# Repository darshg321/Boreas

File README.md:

# Boreas

a flight controller for a rocket.

made this project to both learn how to make flight controllers in general for my drone. making it i got some more practice in routing pcbs and how to read datasheets!
the plan for this board is to be used in a rocket im going to make, where hopefully with the gyro and motor pins i can get it to 1km altitude or higher. little ambitious for my first rocket project but i tihnk it should be fine! for its kind of a big pcb so it'll be hard to fit on the rocket but itll work fine i think. also the sd card will be useful to gain cool telemetry, and i plan to use it to generate interesting graphs that can tell me how to improve the rocket further.

it uses an STM32F7 as an mcu, connected to an imu, barometer, and magnometer. it also has 3 leds, two buttons, a buzzer, and 3 servo motor pins. it can also charge lipo batteries through usb-c! lastly it has an sd card reader for data display!

## Poster (Zine)

## Render

## Schematic

## PCB

## To use

1. plug assembled PCB into computer
2. run ```make flash``` in firmware path after pressing boot and reset buttons to enter flashing mode on the STM32

## BOM

|Item    |Price (USD)|
|--------|-----------|
|PCB     |2          |
|PCBA    |198.65     |
|Shipping|26.51      |
|        |           |
|Total   |227.16     |

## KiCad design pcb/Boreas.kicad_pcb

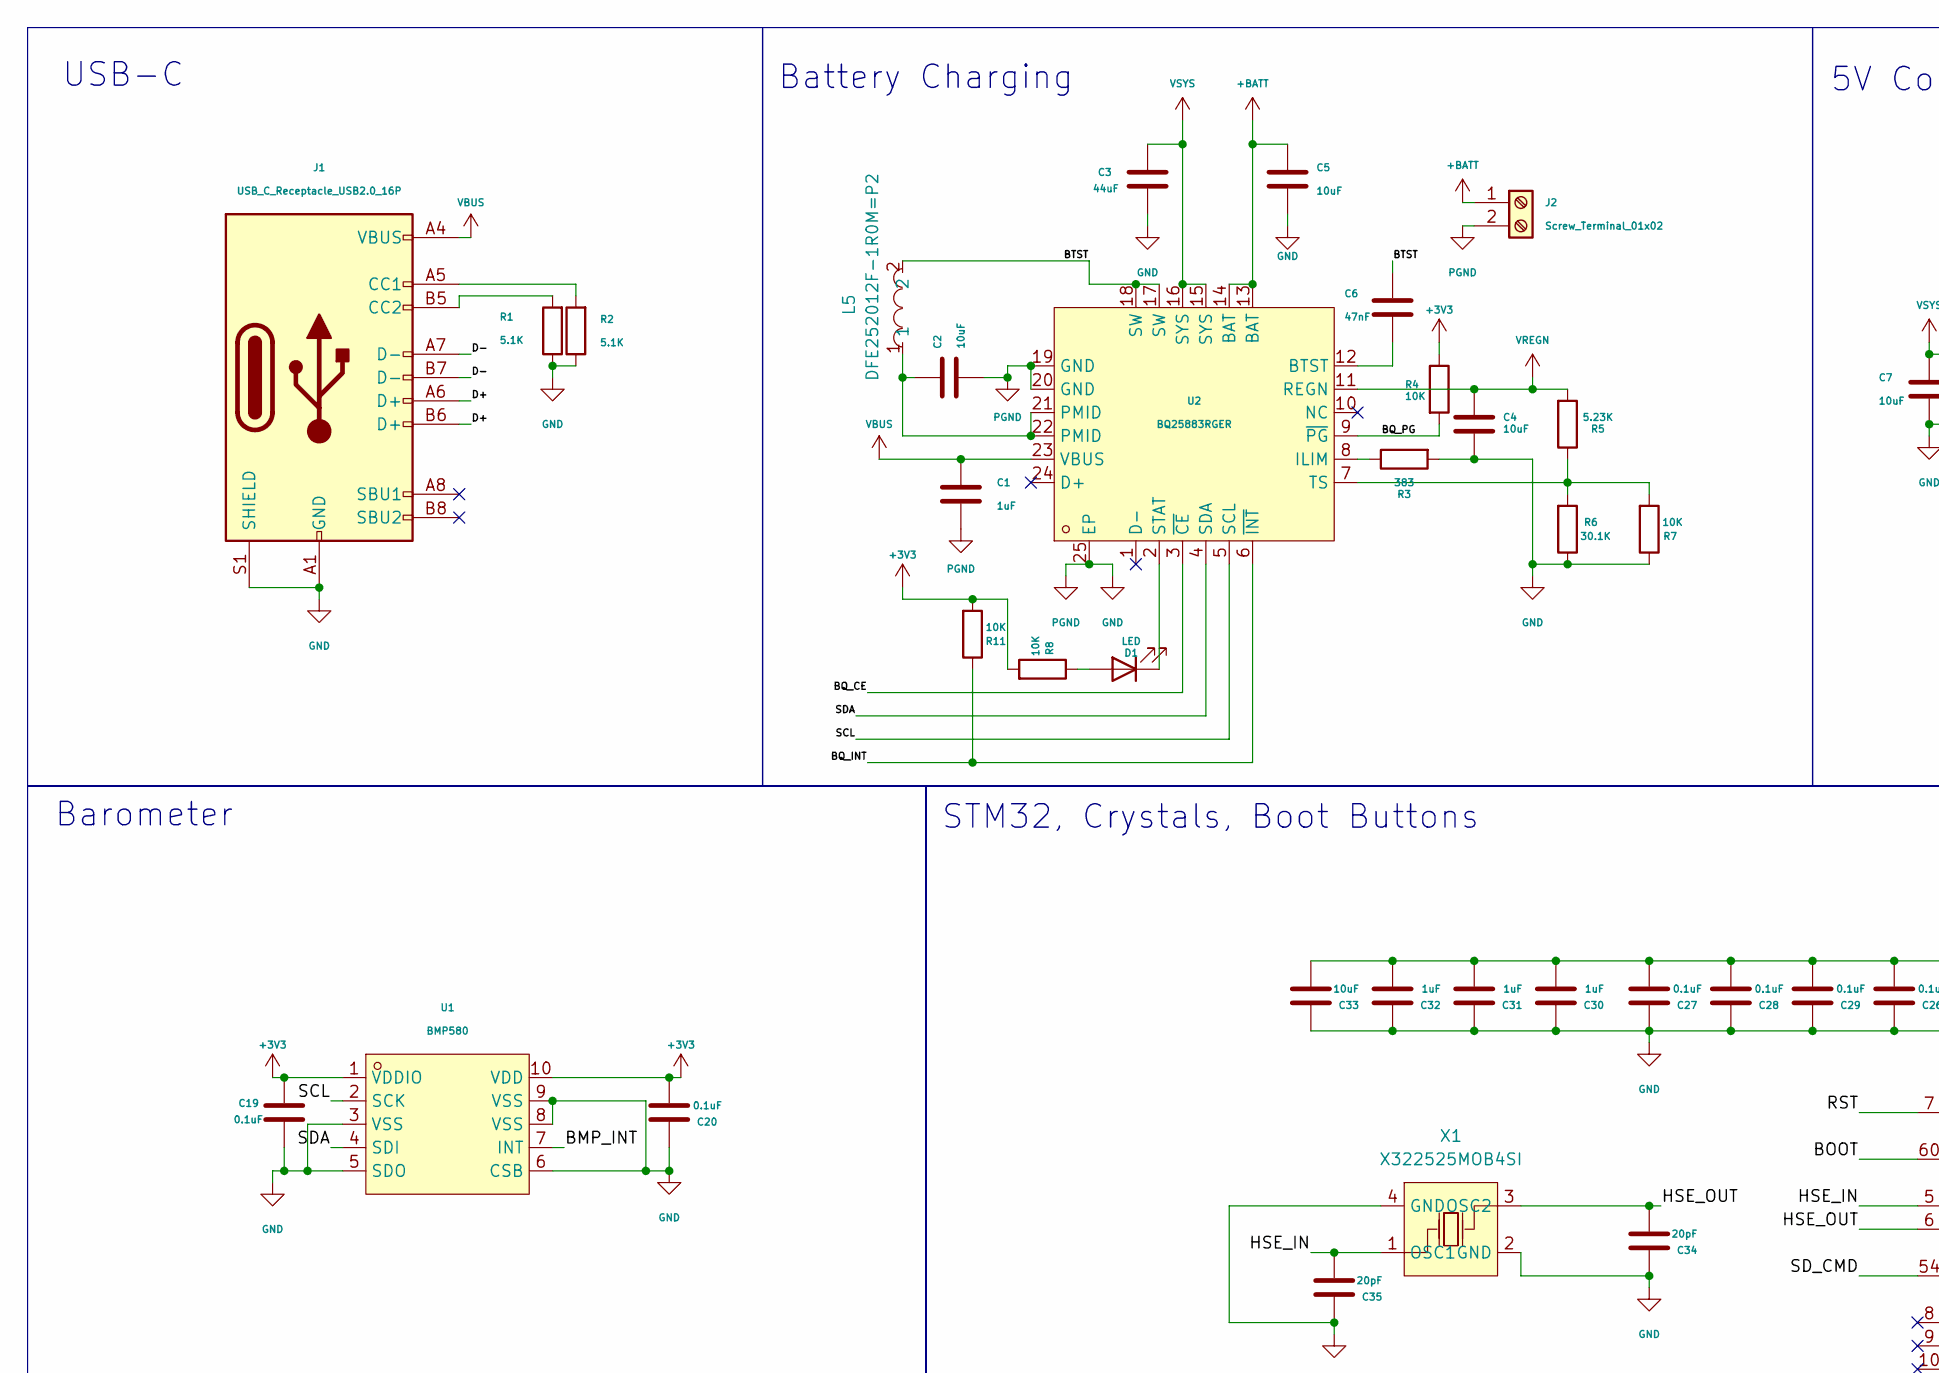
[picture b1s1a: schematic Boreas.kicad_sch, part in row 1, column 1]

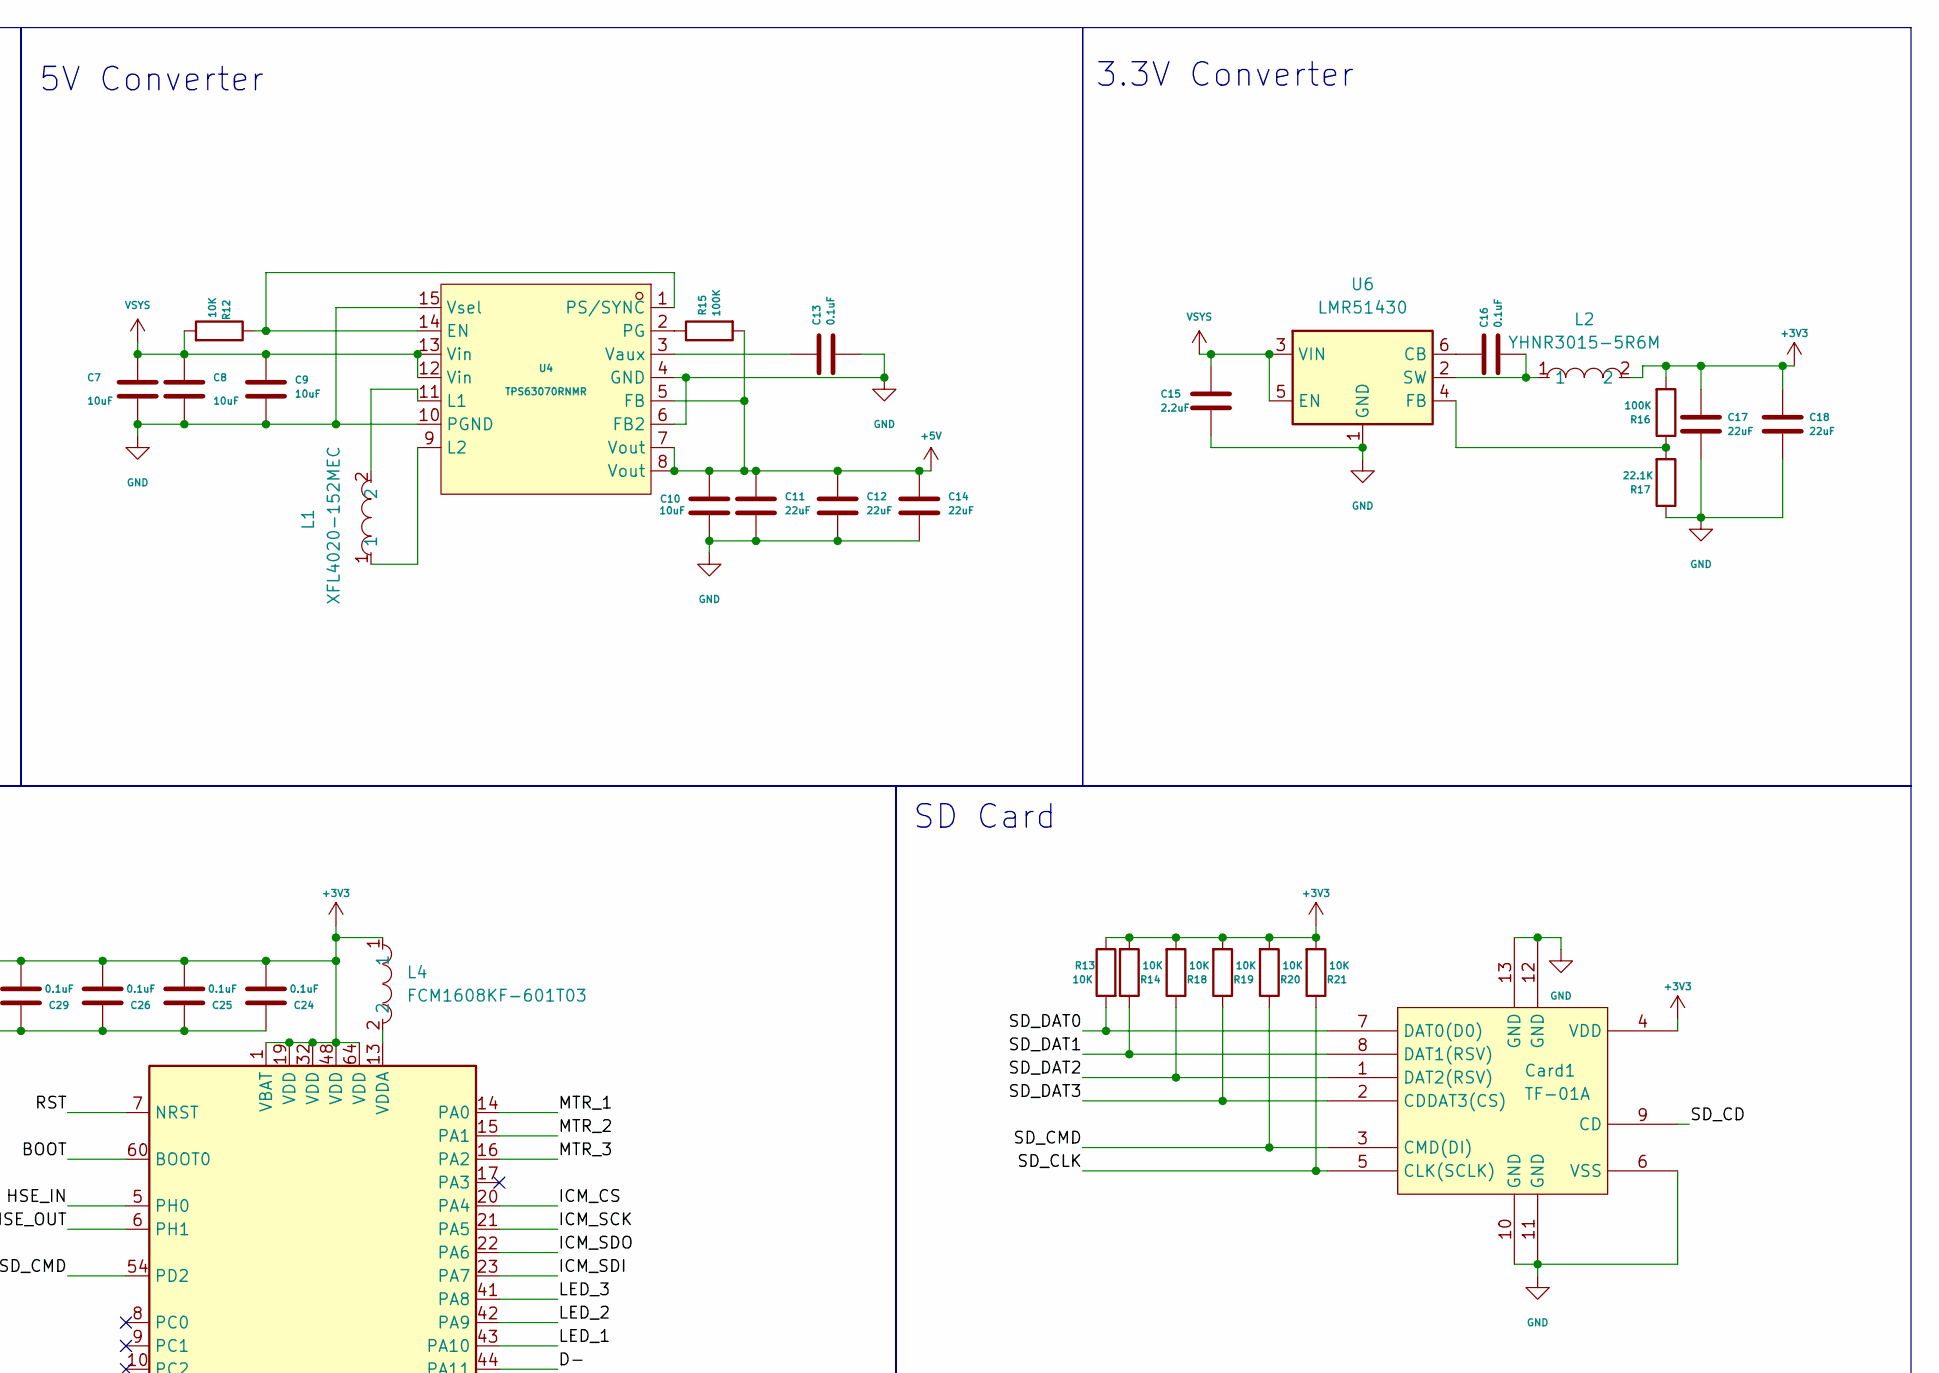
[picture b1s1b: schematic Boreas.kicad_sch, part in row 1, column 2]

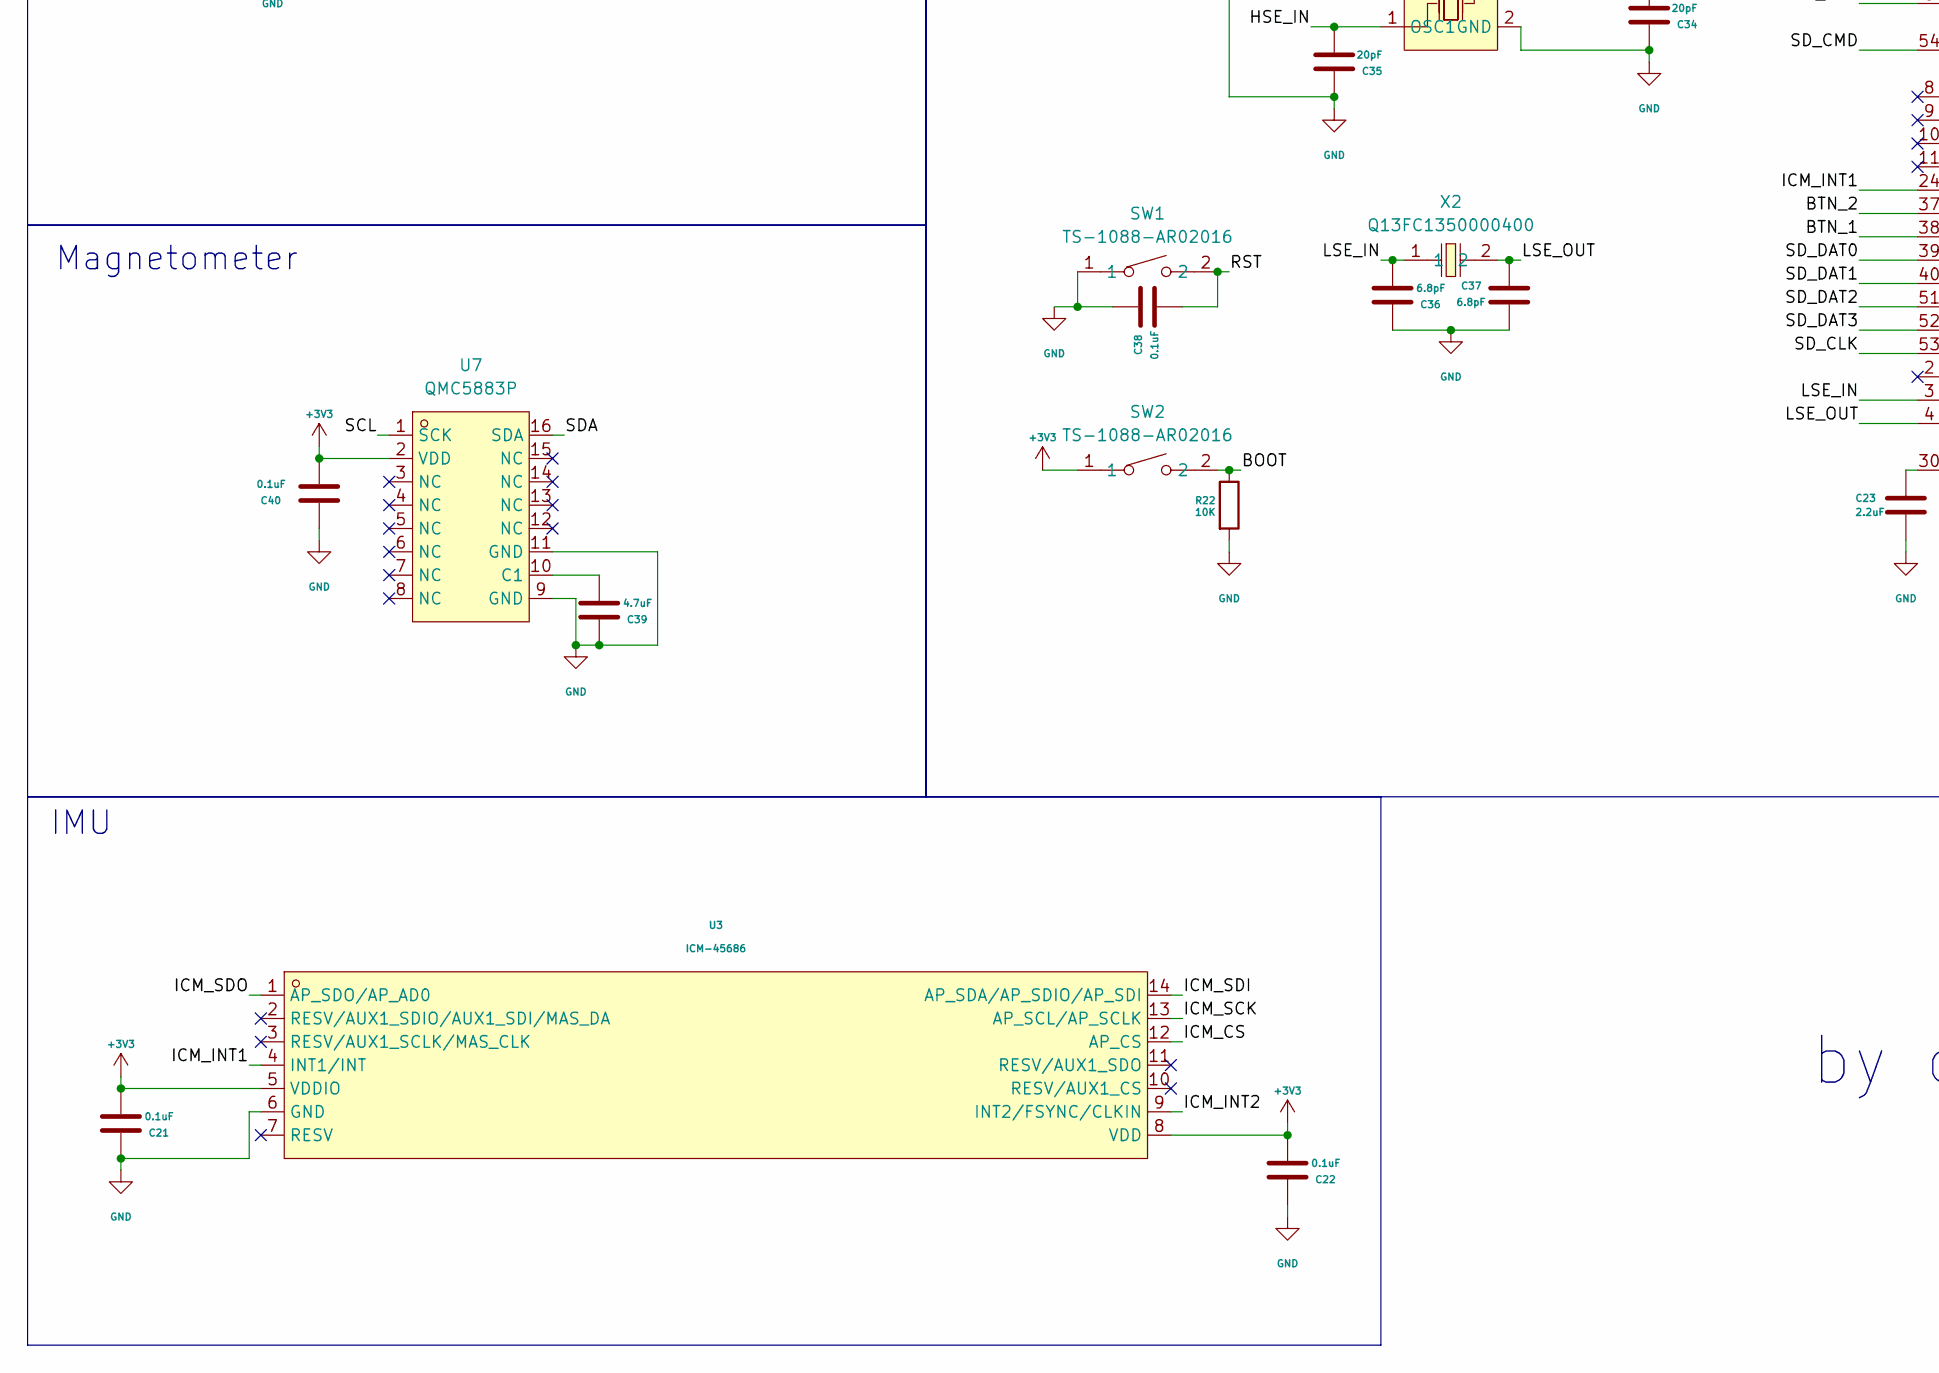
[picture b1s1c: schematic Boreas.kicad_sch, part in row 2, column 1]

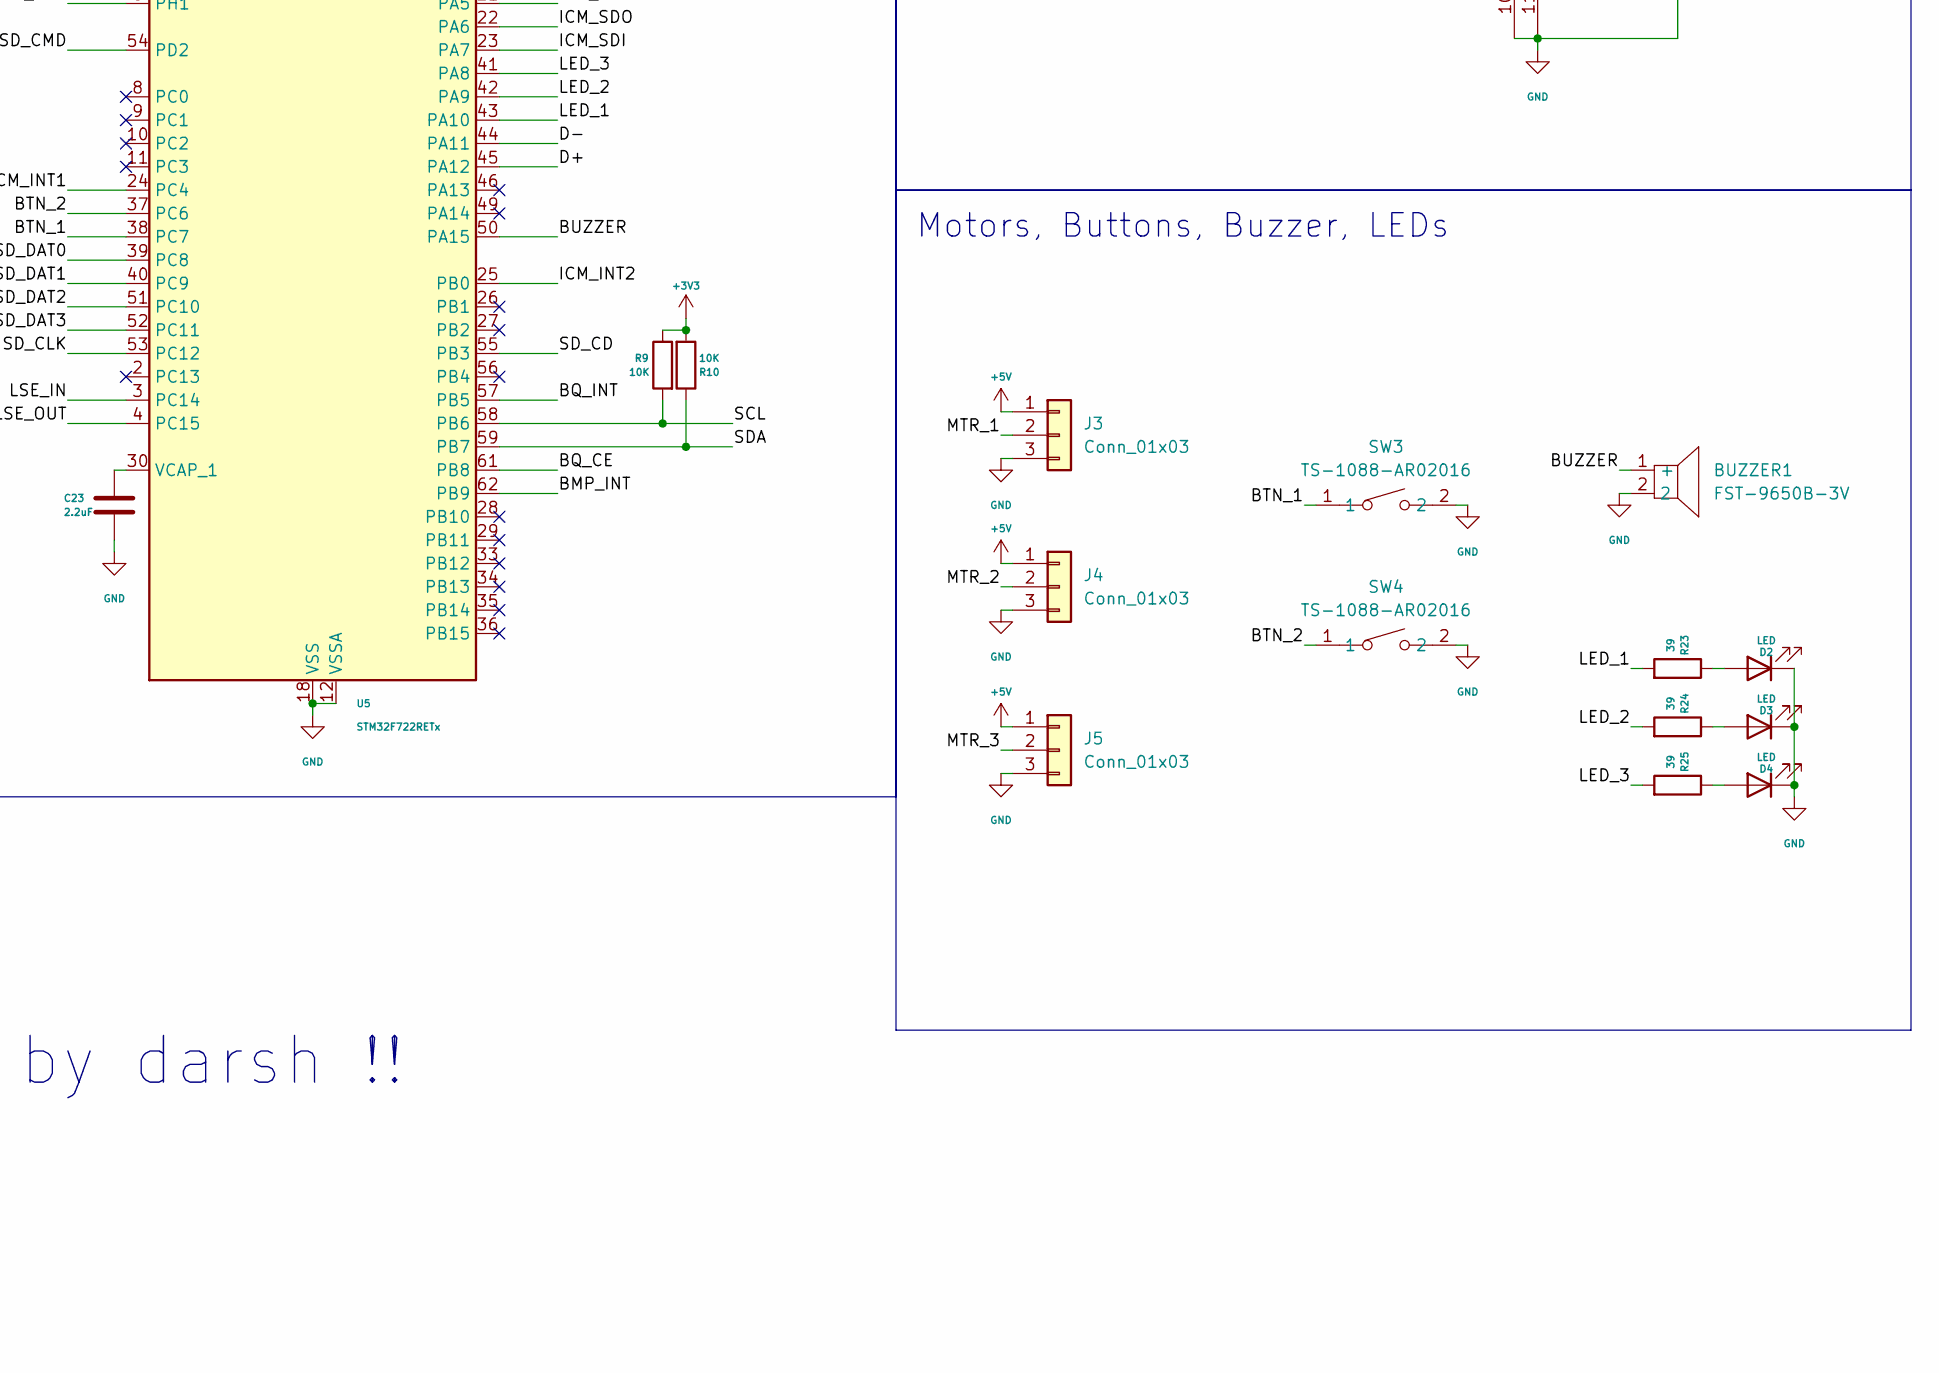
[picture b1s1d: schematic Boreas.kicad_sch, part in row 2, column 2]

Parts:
BUZZER1: FST-9650B-3V; BUZ-SMD_L9.6-W9.6-LS10.0-R; MPN FUET-9650B-3V; LCSC Part C391032
C1, C30, C31, C32: 1uF; C_0402_1005Metric
C2, C4, C5, C7, C8, C9, C10, C33: 10uF; C_0603_1608Metric
C3: 44uF; C_0805_2012Metric
C6: 47nF; C_0402_1005Metric
C11, C12, C14, C17, C18: 22uF; C_0805_2012Metric
C13, C16, C19, C20, C21, C22, C24, C25, C26, C27, C28, C29, C38, C40: 0.1uF; C_0402_1005Metric
C15, C23: 2.2uF; C_0402_1005Metric
C34, C35: 20pF; C_0402_1005Metric
C36, C37: 6.8pF; C_0402_1005Metric
C39: 4.7uF; C_0603_1608Metric
Card1: TF-01A; TF-SMD_TF-01A; MPN TF-01A; LCSC Part C91145
D1, D2, D3, D4: LED; LED_0603_1608Metric
J1: USB_C_Receptacle_USB2.0_16P; USB_C_Receptacle_HRO_TYPE-C-31-M-12
J2: Screw_Terminal_01x02; TerminalBlock_Xinya_XY308-2.54-2P_1x02_P2.54mm_Horizontal
J3, J4, J5: Conn_01x03; PinHeader_1x03_P2.54mm_Vertical
L1: XFL4020-152MEC; IND-SMD_L4.0-W4.0-A; MPN XFL4020-152MEC; LCSC Part C3033018
L2: YHNR3015-5R6M; IND-SMD_L3.0-W3.0; MPN YHNR3015-5R6M; LCSC Part C18236327
L4: FCM1608KF-601T03; L0603; MPN FCM1608KF-601T03; LCSC Part C141723
L5: DFE252012F-1R0M=P2; L2520; MPN DFE252012F-1R0M=P2; LCSC Part C435392
R1, R2: 5.1K; R_0402_1005Metric
R3: 383; R_0402_1005Metric
R4, R7, R8, R9, R10, R11, R12, R13, R14, R18, R19, R20, R21, R22: 10K; R_0402_1005Metric
R5: 5.23K; R_0402_1005Metric
R6: 30.1K; R_0402_1005Metric
R15, R16: 100K; R_0402_1005Metric
R17: 22.1K; R_0402_1005Metric
R23, R24, R25: 39; R_0402_1005Metric
SW1, SW2, SW3, SW4: TS-1088-AR02016; SW-SMD_L3.9-W3.0-P4.45; MPN TS-1088-AR02016; LCSC Part C720477
U1: BMP580; LGA-10_L2.0-W2.0-P0.50-TL_BMP580; MPN BMP580; LCSC Part C22391138
U2: BQ25883RGER; VFQFPN-24_L4.0-W4.0-P0.50-BL-EP2.8; MPN BQ25883RGER; LCSC Part C544362
U3: ICM-45686; LGA-14_L3.0-W2.5-P0.50-TL; MPN ICM-45686; LCSC Part C22459454
U4: TPS63070RNMR; VQFN-15_L3.0-W2.5-P0.50-BL; MPN TPS63070RNMR; LCSC Part C109322
U5: STM32F722RETx; LQFP-64_10x10mm_P0.5mm
U6: LMR51430; SOT-23-6
U7: QMC5883P; LGA-16_L3.0-W3.0-P0.50-BL_SQ; MPN QMC5883P; LCSC Part C2847467
X1: X322525MOB4SI; CRYSTAL-SMD_4P-L3.2-W2.5-BL; MPN X322525MOB4SI; LCSC Part C9006
X2: Q13FC1350000400; FC-135R_L3.2-W1.5; MPN Q13FC13500004; LCSC Part C32346

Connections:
+3V3: C17.1, C18.1, C19.1, C20.2, C21.2, C22.2, C24.2, C25.2, C26.2, C27.2, C28.2, C29.2, C30.2, C31.2, C32.2, C33.2, C40.2, Card1.4 (VDD), L2.2, L4.1, R4.1, R8.2, R9.1, R10.2, R11.2, R13.1, R14.2, R16.2, R18.2, R19.2, R20.2, R21.2, SW2.1, U1.1 (VDDIO), U1.10 (VDD), U3.5 (VDDIO), U3.8 (VDD), U5.1 (VBAT), U5.19 (VDD), U5.32 (VDD), U5.48 (VDD), U5.64 (VDD), U7.2 (VDD)
+5V: C10.2, C11.1, C12.1, C14.1, J3.1, J4.1, J5.1, R15.2, U4.5 (FB), U4.7 (Vout), U4.8 (Vout)
+BATT: C5.1, J2.1, U2.13 (BAT), U2.14 (BAT)
/BMP_INT: U1.7 (INT), U5.62 (PB9)
/BOOT: R22.1, SW2.2, U5.60 (BOOT0)
/BQ_CE: U2.3 (~CE), U5.61 (PB8)
/BQ_INT: R11.1, U2.6 (~INT), U5.57 (PB5)
/BQ_PG: R4.2, U2.9 (~PG)
/BTN_1: SW3.1, U5.38 (PC7)
/BTN_2: SW4.1, U5.37 (PC6)
/BTST: C6.1, L5.2, U2.17 (SW), U2.18 (SW)
/BUZZER: BUZZER1.1 (+), U5.50 (PA15)
/D+: J1.A6 (D+), J1.B6 (D+), U5.45 (PA12)
/D-: J1.A7 (D-), J1.B7 (D-), U5.44 (PA11)
/HSE_IN: C35.2, U5.5 (PH0), X1.1 (OSC1)
/HSE_OUT: C34.2, U5.6 (PH1), X1.3 (OSC2)
/ICM_CS: U3.12 (AP_CS), U5.20 (PA4)
/ICM_INT1: U3.4 (INT1/INT), U5.24 (PC4)
/ICM_INT2: U3.9 (INT2/FSYNC/CLKIN), U5.25 (PB0)
/ICM_SCK: U3.13 (AP_SCL/AP_SCLK), U5.21 (PA5)
/ICM_SDI: U3.14 (AP_SDA/AP_SDIO/AP_SDI), U5.23 (PA7)
/ICM_SDO: U3.1 (AP_SDO/AP_AD0), U5.22 (PA6)
/LED_1: R23.2, U5.43 (PA10)
/LED_2: R24.2, U5.42 (PA9)
/LED_3: R25.2, U5.41 (PA8)
/LSE_IN: C36.2, U5.3 (PC14), X2.1
/LSE_OUT: C37.1, U5.4 (PC15), X2.2
/MTR_1: J3.2, U5.14 (PA0)
/MTR_2: J4.2, U5.15 (PA1)
/MTR_3: J5.2, U5.16 (PA2)
/RST: C38.2, SW1.2, U5.7 (NRST)
/SCL: R9.2, U1.2 (SCK), U2.5 (SCL), U5.58 (PB6), U7.1 (SCK)
/SDA: R10.1, U1.4 (SDI), U2.4 (SDA), U5.59 (PB7), U7.16 (SDA)
/SD_CD: Card1.9 (CD), U5.55 (PB3)
/SD_CLK: Card1.5 (CLK(SCLK)), R21.1, U5.53 (PC12)
/SD_CMD: Card1.3 (CMD(DI)), R20.1, U5.54 (PD2)
/SD_DAT0: Card1.7 (DAT0(D0)), R13.2, U5.39 (PC8)
/SD_DAT1: Card1.8 (DAT1(RSV)), R14.1, U5.40 (PC9)
/SD_DAT2: Card1.1 (DAT2(RSV)), R18.1, U5.51 (PC10)
/SD_DAT3: Card1.2 (CDDAT3(CS)), R19.1, U5.52 (PC11)
GND: BUZZER1.2, C1.2, C2.2, C3.1, C4.2, C5.2, C7.2, C8.2, C9.2, C10.1, C11.2, C12.2, C13.2, C14.2, C15.2, C17.2, C18.2, C19.2, C20.1, C21.1, C22.1, C23.2, C24.1, C25.1, C26.1, C27.1, C28.1, C29.1, C30.1, C31.1, C32.1, C33.1, C34.1, C35.1, C36.1, C37.2, C38.1, C39.1, C40.1, Card1.6 (VSS), Card1.10 (GND), Card1.11 (GND), Card1.12 (GND), Card1.13 (GND), D2.1 (K), D3.1 (K), D4.1 (K), J1.A1 (GND), J1.A12 (GND), J1.B1 (GND), J1.B12 (GND), J1.S1 (SHIELD), J2.2, J3.3, J4.3, J5.3, R1.1, R2.1, R3.2, R6.1, R7.1, R17.1, R22.2, SW1.1, SW3.2, SW4.2, U1.3 (VSS), U1.5 (SDO), U1.6 (CSB), U1.8 (VSS), U1.9 (VSS), U2.19 (GND), U2.20 (GND), U2.25 (EP), U3.6 (GND), U4.4 (GND), U4.6 (FB2), U4.10 (PGND), U4.15 (Vsel), U5.12 (VSSA), U5.18 (VSS), U5.31 (VSS), U5.47 (VSS), U5.63 (VSS), U6.1 (GND), U7.9 (GND), U7.11 (GND), X1.2 (GND), X1.4 (GND)
unnamed: C2.1, L5.1, U2.21 (PMID), U2.22 (PMID)
unnamed: D1.2 (A), R8.1
unnamed: D1.1 (K), U2.2 (STAT)
unnamed: D2.2 (A), R23.1
unnamed: D3.2 (A), R24.1
unnamed: D4.2 (A), R25.1
unnamed: J1.A5 (CC1), R2.2
unnamed: J1.B5 (CC2), R1.2
unnamed: C6.2, U2.12 (BTST)
unnamed: R3.1, U2.8 (ILIM)
unnamed: R5.1, R6.2, R7.2, U2.7 (TS)
unnamed: R12.1, U4.1 (PS/SYNC), U4.14 (EN)
unnamed: L1.2, U4.11 (L1)
unnamed: L1.1, U4.9 (L2)
unnamed: R15.1, U4.2 (PG)
unnamed: C13.1, U4.3 (Vaux)
unnamed: C23.1, U5.30 (VCAP_1)
unnamed: L4.2, U5.13 (VDDA)
unnamed: C16.1, U6.6 (CB)
unnamed: R16.1, R17.2, U6.4 (FB)
unnamed: C16.2, L2.1, U6.2 (SW)
unnamed: C39.2, U7.10 (C1)
VBUS: C1.1, J1.A4 (VBUS), J1.A9 (VBUS), J1.B4 (VBUS), J1.B9 (VBUS), U2.23 (VBUS)
VREGN: C4.1, R5.2, U2.11 (REGN)
VSYS: C3.2, C7.1, C8.1, C9.1, C15.1, R12.2, U2.15 (SYS), U2.16 (SYS), U4.12 (Vin), U4.13 (Vin), U6.3 (VIN), U6.5 (EN)

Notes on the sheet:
Magnetometer
Motors, Buttons, Buzzer, LEDs
SD Card
3.3V Converter
USB-C
Barometer
5V Converter
Battery Charging
IMU
by darsh !!
STM32, Crystals, Boot Buttons

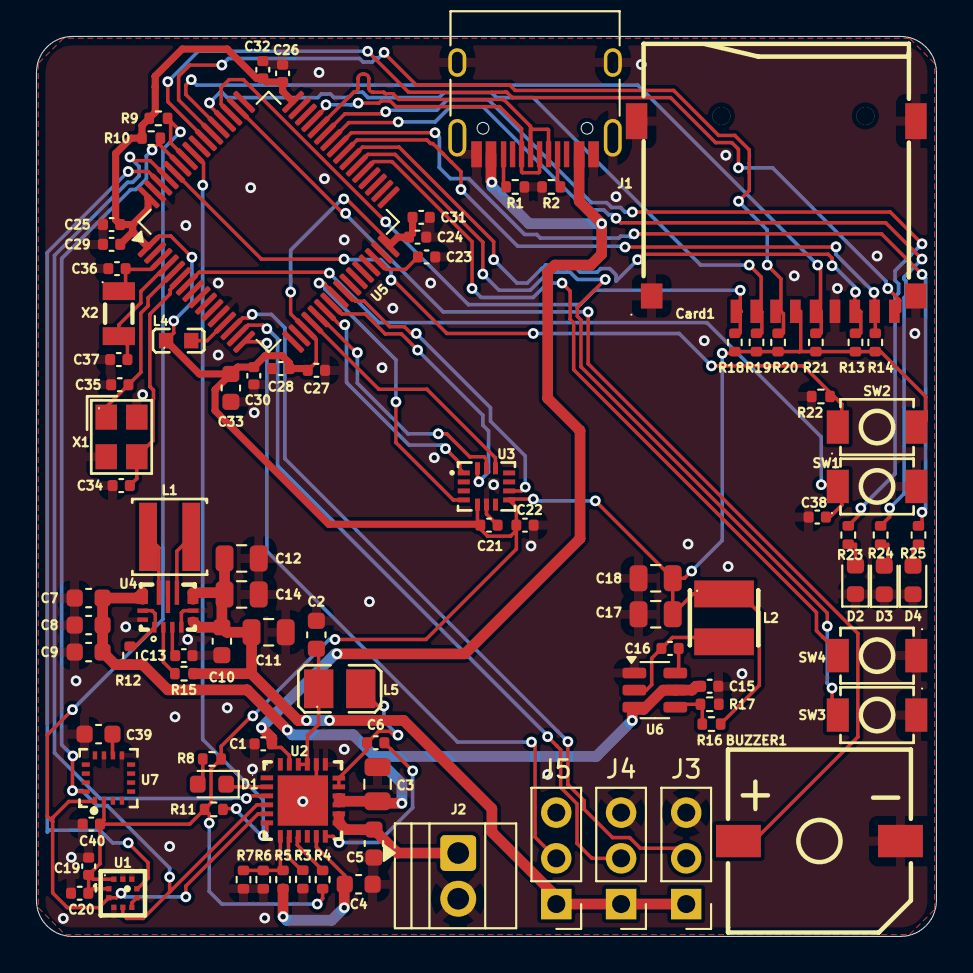
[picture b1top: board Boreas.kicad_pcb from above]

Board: 2 copper layers, 50.0 x 50.0 mm, 93 parts (0 on the bottom side), 66 nets.

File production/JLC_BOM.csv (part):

"JLCPCB BOM Tool - BOM Matching","","","","","","","","","","","","","","","","",""
"BOM name：production_bom-JLCPCB Assembly Order.xlsx","","","Download Time：2026-06-12 11:30:08","","","","* Our matching results are updated in real-time, but stock and prices may change. 
If it's been over 24 hours, please re-match before placing your order.","","","","","","","","","",""
"PCB Assembled Qty：5","","","Est. Total Price：69.0311","","","","","","","","","","","","","",""
"Your BOM","","","","","Matched Parts","","","","","","","Order Information","","","","",""
"Top Designator","Bottom Designator","Comment","Footprint","JLCPCB Part #","Matches","Part # ","Manufacturer","Footprint","Description","Category","Warning","JLCPCB Part #","Product link","Lib Type","Qty","Source","Total Price ($)"
"BUZZER1","","FST-9650B-3V","BUZ-SMD_L9.6-W9.6-LS10.0-R","","Select by System","FUET-9650B-3V","FUET","SMD,9.6x9.6mm","-20℃~+80℃ 2V~5V 30mA 3V 3kHz 5.5mm 85dB 9.6mm 9.6mm Active Buzzer (Built-in Driving Circuit) Electromagnetic SMD,9.6x9.6mm Buzzers ROHS","Buzzers","","C391032","https://jlcpcb.com/partdetail/FUET-FUET_9650B3V/C391032","Extended","2","2 JLCPCB","1.1802"
"C1,C30,C31,C32","","1uF","0402","","Select by System","CL05A105KA5NQNC","Samsung Electro-Mechanics","0402","1uF 25V X5R ±10% 0402 Multilayer Ceramic Capacitors MLCC - SMD/SMT ROHS","Multilayer Ceramic Capacitors MLCC - SMD/SMT","","C52923","https://jlcpcb.com/partdetail/53938-CL05A105KA5NQNC/C52923","Basic","20","20 JLCPCB","0.138"
"C3","","44uF","0805","","Select by Customer","CL21A476MQYNNNE","Samsung Electro-Mechanics","0805","47uF 6.3V X5R ±20% 0805 Multilayer Ceramic Capacitors MLCC - SMD/SMT ROHS","Multilayer Ceramic Capacitors MLCC - SMD/SMT","","C16780","https://jlcpcb.com/partdetail/17464-CL21A476MQYNNNE/C16780","Basic","8","8 JLCPCB","1.0848"
"C6","","47nF","0402","","Select by Customer","0402B473K500NT","FH (Guangdong Fenghua Advanced Tech)","0402","47nF 50V X7R ±10% 0402 Multilayer Ceramic Capacitors MLCC - SMD/SMT ROHS","Multilayer Ceramic Capacitors MLCC - SMD/SMT","","C82219","https://jlcpcb.com/partdetail/83376-0402B473K500NT/C82219","Extended","20","20 JLCPCB","0.068"
"C10,C2,C33,C4,C5,C7,C8,C9","","10uF","0603","","Select by System","CL10A106KP8NNNC","Samsung Electro-Mechanics","0603","10V 10uF X5R ±10% 0603 Multilayer Ceramic Capacitors MLCC - SMD/SMT ROHS","Multilayer Ceramic Capacitors MLCC - SMD/SMT","","C19702","https://jlcpcb.com/partdetail/20411-CL10A106KP8NNNC/C19702","Basic","26","26 JLCPCB","0.4498"
"C11,C12,C14,C17,C18","","22uF","0805","","Select by System","CL21A226MAQNNNE","Samsung Electro-Mechanics","0805","22uF 25V X5R ±20% 0805 Multilayer Ceramic Capacitors MLCC - SMD/SMT ROHS","Multilayer Ceramic Capacitors MLCC - SMD/SMT","","C45783","https://jlcpcb.com/partdetail/46786-CL21A226MAQNNNE/C45783","Basic","18","18 JLCPCB","1.7082"
"C13,C16,C19,C20,C21,C22,C24,C25,C26,C27,C28,C29,C38,C40","","0.1uF","0402","","Unconfirmed","CL05B104KO5NNNC","Samsung Electro-Mechanics","0402","100nF 16V X7R ±10% 0402 Multilayer Ceramic Capacitors MLCC - SMD/SMT ROHS","Multilayer Ceramic Capacitors MLCC - SMD/SMT","1.The comment (CL05B104KO5NNNC) of this part does not match the one (0.1uF) provided in your BOM. Please confirm;","C1525","https://jlcpcb.com/partdetail/1877-CL05B104KO5NNNC/C1525","Basic","38","38 JLCPCB","0.0874"
"C15,C23","","2.2uF","0402","","Select by System","CL05A225MQ5NSNC","Samsung Electro-Mechanics","0402","2.2uF 6.3V X5R ±20% 0402 Multilayer Ceramic Capacitors MLCC - SMD/SMT ROHS","Multilayer Ceramic Capacitors MLCC - SMD/SMT","","C12530","https://jlcpcb.com/partdetail/13164-CL05A225MQ5NSNC/C12530","Basic","20","20 JLCPCB","0.154"
"C34,C35","","20pF","0402","","Select by System","0402CG200J500NT","FH (Guangdong Fenghua Advanced Tech)","0402","20pF 50V C0G ±5% 0402 Multilayer Ceramic Capacitors MLCC - SMD/SMT ROHS","Multilayer Ceramic Capacitors MLCC - SMD/SMT","","C1554","https://jlcpcb.com/partdetail/1906-0402CG200J500NT/C1554","Basic","20","20 JLCPCB","0.042"
"C36,C37","","6.8pF","0402","","Select by Customer","0402CG6R8C500NT","FH (Guangdong Fenghua Advanced Tech)","0402","50V 6.8pF C0G 0402 Multilayer Ceramic Capacitors MLCC - SMD/SMT ROHS","Multilayer Ceramic Capacitors MLCC - SMD/SMT","","C1576","https://jlcpcb.com/partdetail/1928-0402CG6R8C500NT/C1576","Extended","20","20 JLCPCB","0.048"
"C39","","4.7uF","0603","","Select by System","CL10A475KO8NNNC","Samsung Electro-Mechanics","0603","16V 4.7uF X5R ±10% 0603 Multilayer Ceramic Capacitors MLCC - SMD/SMT ROHS","Multilayer Ceramic Capacitors MLCC - SMD/SMT","","C19666","https://jlcpcb.com/partdetail/20375-CL10A475KO8NNNC/C19666","Basic","20","20 JLCPCB","0.368"
"CARD1","","TF-01A","TF-SMD_TF-01A","","Select by System","TF-01A","Korean Hroparts Elec","SMD","1.85mm Connector and Ejector MicroSD Card (TF Card) Push-Push With Locating Pins SMD SD Card / Memory Card Connector ROHS","SD Card / Memory Card Connector","","C91145","https://jlcpcb.com/partdetail/Korean_HropartsElec-TF01A/C91145","Extended","2","2 JLCPCB","0.3806"
"D1,D2,D3,D4","","LED","0603","","Select by Customer","KT-0603G","Hubei KENTO Elec","0603","-40℃~+85℃ 1.6mm x 0.8mm square LED 100mW 120° 3.1V 430mcd 513nm~528nm 525nm 5mA Discrete Diode Emerald Green Water Clear 0603 LED Indication - Discrete ROHS","LED Indication - Discrete","1.The comment (KT-0603G) of this part does not match the one (LED) provided in your BOM. Please confirm;","C12624","https://jlcpcb.com/partdetail/Hubei_KENTOElec-KT0603G/C12624","Extended","20","20 JLCPCB","0.242"
"J1","","USB_C_Receptacle_USB2.0_16P","USB_C_Receptacle_HRO_TYPE-C-31-M-12","","Select by Customer","TYPE-C-31-M-12","Korean Hroparts Elec","SMD","-30℃~+80℃ 1 10,000 cycles 16P 20V 5A 7.35mm Female Surface Mount, Right Angle Type-C SMD USB Connectors ROHS","USB Connectors","","C165948","https://jlcpcb.com/partdetail/Korean_HropartsElec-TYPE_C_31_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","Extended","2","2 JLCPCB","0.3684"
"L1","","XFL4020-152MEC","IND-SMD_L4.0-W4.0-A","","Select by System","XFL4020-152MEC","Coilcraft","SMD,4x4mm","1.5uH 14.4mΩ 4.6A 9.1A Magnetic Shielded Inductor ±20% SMD,4x4mm Power Inductors ROHS","Power Inductors","","C3033018","https://jlcpcb.com/partdetail/Coilcraft-XFL4020152MEC/C3033018","Extended","2","2 JLCPCB","2.7506"
"L2","","YHNR3015-5R6M","IND-SMD_L3.0-W3.0","","Select by System","YHNR3015-5R6M","YJYCOIN","SMD,3x3mm","2.2A 250mΩ 5.6uH Magnetic Shielded Inductor ±20% SMD,3x3mm Power Inductors ROHS","","","C18236327","https://jlcpcb.com/partdetail/YJYCOIN-YHNR30155R6M/C18236327","Extended","15","15 JLCPCB","1.1235"
"L4","","FCM1608KF-601T03","L0603","","Select by Customer","BLM18EG601SN1D","Murata Electronics","0603","-55℃~+125℃ 1 350mΩ 500mA 600Ω@100MHz ±25% 0603 Ferrite Beads ROHS","Ferrite Beads","","C20345","https://jlcpcb.com/partdetail/MurataElectronics-BLM18EG601SN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","Extended","10","10 JLCPCB","0.81"
"L5","","DFE252012F-1R0M=P2","L2520","","Select by System","DFE252012F-1R0M=P2","Murata Electronics","1008","1uH 3.3A 4.7A 40mΩ ±20% 1008 Power Inductors ROHS","Power Inductors","","C435392","https://jlcpcb.com/partdetail/MurataElectronics-DFE252012F_1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","Extended","5","5 JLCPCB","0.909"
"R1,R2","","5.1K","0402","","Unconfirmed","0402WGF5101TCE","UNI-ROYAL(Uniroyal Elec)","0402","-55℃~+155℃ 5.1kΩ 50V 62.5mW Thick Film Resistor ±1% ±100ppm/℃ 0402 Chip Resistor - Surface Mount ROHS","Chip Resistor - Surface Mount","1.The comment (0402WGF5101TCE) of this part does not match the one (5.1K) provided in your BOM. Please confirm;","C25905","https://jlcpcb.com/partdetail/26648-0402WGF5101TCE/C25905","Basic","20","20 JLCPCB","0.018"
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
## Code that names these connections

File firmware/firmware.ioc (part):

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Mcu.Name=STM32F722R(C-E)Tx
Mcu.Package=LQFP64
Mcu.UserName=STM32F722RETx
PA0-WKUP.Signal=S_TIM2_CH1_ETR
PA1.Signal=S_TIM2_CH2
PA10.GPIOParameters=GPIO_Label
PA10.GPIO_Label=LED_1
PA10.Signal=GPIO_Output
PA11.Mode=Host_Only
PA11.Signal=USB_OTG_FS_DM
PA12.Mode=Host_Only
PA12.Signal=USB_OTG_FS_DP
PA2.Signal=S_TIM2_CH3
PA4.Mode=NSS_Signal_Hard_Output
PA4.Signal=SPI1_NSS
PA5.Mode=Full_Duplex_Master
PA5.Signal=SPI1_SCK
PA6.Mode=Full_Duplex_Master
PA6.Signal=SPI1_MISO
PA7.Mode=Full_Duplex_Master
PA7.Signal=SPI1_MOSI
PA8.GPIOParameters=GPIO_Label
PA8.GPIO_Label=LED_3
PA8.Signal=GPIO_Output
PA9.GPIOParameters=GPIO_Label
PA9.GPIO_Label=LED_2
PA9.Signal=GPIO_Output
PB0.GPIOParameters=GPIO_Label
PB0.GPIO_Label=ICM_INT2
PB0.Signal=GPXTI0
PB15.GPIOParameters=GPIO_Label
PB15.GPIO_Label=BUZZER
PB15.Signal=GPIO_Output
PB3.GPIOParameters=GPIO_Label
PB3.GPIO_Label=SD_CS
PB3.Signal=GPIO_Input
PB5.GPIOParameters=GPIO_Label
PB5.GPIO_Label=BQ_INT
PB5.Signal=GPXTI5
PB6.Mode=I2C
PB6.Signal=I2C1_SCL
PB7.Mode=I2C
PB7.Signal=I2C1_SDA
PB8.GPIOParameters=GPIO_Label
PB8.GPIO_Label=BQ_CE
PB8.Signal=GPIO_Output
PB9.GPIOParameters=GPIO_Label
PB9.GPIO_Label=BMP_INT
PB9.Signal=GPXTI9
PC10.Mode=SD_4_bits_Wide_bus
PC10.Signal=SDMMC1_D2
PC11.Mode=SD_4_bits_Wide_bus
PC11.Signal=SDMMC1_D3
PC12.Mode=SD_4_bits_Wide_bus
PC12.Signal=SDMMC1_CK
PC14-OSC32_IN.Mode=LSE-External-Oscillator
PC14-OSC32_IN.Signal=RCC_OSC32_IN
PC15-OSC32_OUT.Mode=LSE-External-Oscillator
PC15-OSC32_OUT.Signal=RCC_OSC32_OUT
PC4.GPIOParameters=GPIO_Label
PC4.GPIO_Label=ICM_INT1
PC4.Signal=GPXTI4
PC6.GPIOParameters=GPIO_Label
PC6.GPIO_Label=BTN_2
PC6.Signal=GPIO_Input
PC7.GPIOParameters=GPIO_Label
PC7.GPIO_Label=BTN_1
PC7.Signal=GPIO_Input
PC8.Mode=SD_4_bits_Wide_bus
PC8.Signal=SDMMC1_D0
PC9.Mode=SD_4_bits_Wide_bus
PC9.Signal=SDMMC1_D1
PD2.Mode=SD_4_bits_Wide_bus
PD2.Signal=SDMMC1_CMD
PH0-OSC_IN.Mode=HSE-External-Oscillator
PH0-OSC_IN.Signal=RCC_OSC_IN
PH1-OSC_OUT.Mode=HSE-External-Oscillator
PH1-OSC_OUT.Signal=RCC_OSC_OUT
RCC.HSE_VALUE=25000000
board=custom

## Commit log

2026-06-08 schematic done!
2026-06-15 done!
2026-06-15 add poster to readme
2026-06-21 fixes
2026-06-23 fix:
